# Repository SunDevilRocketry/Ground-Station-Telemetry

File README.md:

<h1>Ground Station Telemetry Unit</h1>

<p>Current PCB Revision: 1.0</p>
<p>PCB Part Number: A0005</p>

<p>The Ground Station Telemetry Unit adds wireless connectivity to the Raspberry-Pi 
based ground station computer. The unit is equipped with a socket for an XBee module, as well as a LoRa module.</p>

<p><b>Working Directory Structure:</b></p>

<p>
   doc: documentation
   
   src: source design files, e.g. schematic and PCB layout files

   lib: libraries for schematic symbols and footprints

   production: files needed for pcb fabrication, e.g. gerbers, profile, drill file

   sim: simulation models/files 

   cad: 3d models
  
   img: images of circuit/footprints for github display 
</p>

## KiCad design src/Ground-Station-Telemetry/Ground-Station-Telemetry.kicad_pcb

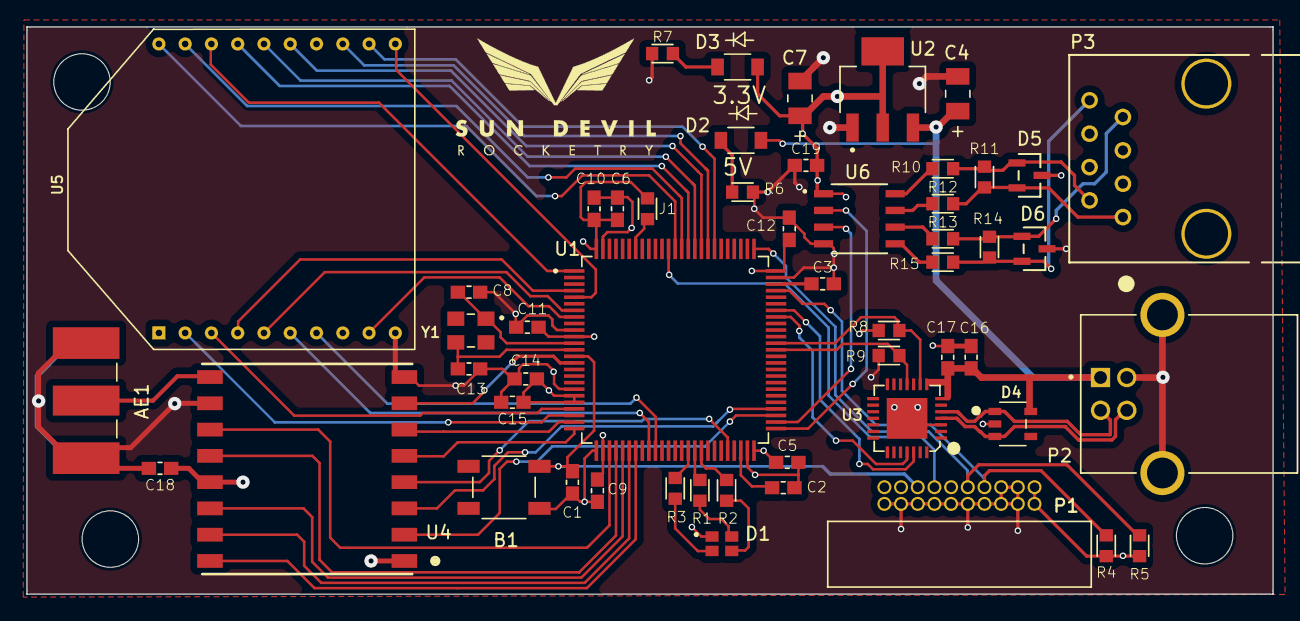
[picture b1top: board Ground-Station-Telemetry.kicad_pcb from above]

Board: 4 copper layers, 94.9 x 43.2 mm, 57 parts (0 on the bottom side), 64 nets.

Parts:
AE1: 142-0701-851
B1: PTS647SM38SMTR2LFS
C1, C5, C9, C10, C11, C12, C14, C17, C18, C19: 0.1uF; CAP_0603
C2, C3: 2.2uF; CAP_0603
C4, C7: 10uF; T491A106K010AT
C6: 4.7uF; CAP_0603
C8, C13: 8pF; CAP_0603
C15, C16: 1uF; CAP_0603
D1: CLMVC-FKA-CL1D1L71BB7C3C3
D2, D3: SML-LX1206GC-TR
D4: SP0504BAHTG
D5, D6: SMBJ36CA-13-F; CDSOT23-SM712
H1, H2, H4: Mounting-Hole; MountingHole_4.3mm_M4_DIN965
J1: Jumper_NO; RES_0603
LOGO1: Logo
P1: 3220-20-0200-00
P2: USB; USB-TypeB
P3: 54602-908LF
R1: 68; RES_0603
R2: 82; RES_0603
R3: 280; RES_0603
R4, R5: 100k; RES_0603
R6, R7: 240; RES_0603
R8: 4.7k; RES_0603
R9: 10k; RES_0603
R10, R12, R13, R15: 10; RES_0603
R11, R14: 100; RES_0603
U1: STM32H750VBTx; STM32H750VBT6
U2: LMS8117AMP-3.3_NOPB; LMS8117AMP-3.3NOPB
U3: CP2102-GMR(QFN28); CP2012-GMR
U4: RFM95W-868S2; RFM95
U5: XB24CDMPIT-001; XBee
U6: SN65HVD71DR
Y1: ECS-240-18-33-JGN-TR

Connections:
3.3V: C5.1, C6.1, C7.1, C9.1, C10.1, C11.1, C12.1, C14.1, C15.1, C18.1, C19.1, D1.1, D3.2, J1.1 (A), P1.1, P1.2, R4.2, R5.2, R8.1, U1.11 (VDD), U1.20 (VREF+), U1.21 (VDDA), U1.27 (VDD), U1.50 (VDD), U1.75 (VDD), U1.100 (VDD), U2.2 (VOUT), U4.13 (3_3V), U5.1 (VCC), U6.1 (VCC)
5V: C4.1, C16.1, C17.1, D2.2, D4.5, P2.1 (VCC), U2.3 (VIN), U3.7 (REGIN), U3.8 (VBUS)
/Connectivity/D+: D4.3, P2.3 (D+), U3.4 (D+)
/Connectivity/D-: D4.1, P2.2 (D-), U3.5 (D-)
A: D5.1, P3.2, R10.2, R11.2
B: D5.2, P3.1, R11.1, R12.2
BOOT: J1.2 (B), U1.94 (BOOT0)
CAP1: C2.1, U1.48 (VCAP1)
CAP2: C3.1, U1.73 (VCAP2)
Earth: AE1.2 (Shield), B1.1, C1.2, C2.2, C3.2, C4.2, C5.2, C6.2, C7.2, C8.2, C9.2, C10.2, C11.2, C12.2, C13.2, C14.2, C15.2, C16.2, C17.2, C18.2, C19.2, D4.2, D5.3, D6.3, P1.3, P1.4, P1.5, P1.6, P1.8, P1.10, P1.12, P1.14, P1.16, P1.18, P1.20, P2.4 (GND), P2.S1 (SHIELD), P2.S2 (SHIELD), R6.1, R7.1, R9.1, U1.10 (VSS), U1.19 (VSSA), U1.26 (VSS), U1.49 (VSS), U1.74 (VSS), U1.99 (VSS), U2.1 (GND), U3.3 (GND), U3.29 (PAD), U4.1 (GND), U4.8 (GND@1), U4.10 (GND@2), U5.10 (GND), U6.4 (GND)
LORA_IO0: U1.30 (PA6), U4.14 (DIO0)
LORA_IO1: U1.31 (PA7), U4.15 (DIO1)
LORA_IO2: U1.32 (PC4), U4.16 (DIO2)
LORA_IO3: U1.28 (PA4), U4.11 (DIO3)
LORA_IO4: U1.29 (PA5), U4.12 (DIO4)
LORA_IO5: U1.15 (PC0), U4.7 (DIO5)
LORA_MISO: U1.53 (PB14), U4.2 (MISO)
LORA_MOSI: U1.54 (PB15), U4.3 (MOSI)
LORA_RST: U1.24 (PA2), U4.6 (RESET)
LORA_SCK: U1.46 (PB10), U4.4 (SCK)
LORA_SS: U1.25 (PA3), U4.5 (NSS)
NRST: B1.3, C1.1, P1.15, U1.14 (NRST)
unnamed: AE1.1 (A), U4.9 (ANT)
unnamed: D1.2, R1.2
unnamed: D1.3, R2.2
unnamed: D1.4, R3.2
unnamed: D2.1, R6.2
unnamed: D3.1, R7.2
unnamed: R10.1, U6.8 (A)
unnamed: R12.1, U6.7 (B)
unnamed: R15.1, U6.5 (Y)
unnamed: R13.1, U6.6 (Z)
OSC_IN: C8.1, U1.12 (PH0), Y1.1
OSC_OUT: C13.1, U1.13 (PH1), Y1.3
RS485_RX: U1.51 (PB12), U6.2 (R)
RS485_TX: U1.52 (PB13), U6.3 (D)
STATUS_B: R1.1, U1.41 (PE11)
STATUS_G: R2.1, U1.42 (PE12)
STATUS_R: R3.1, U1.40 (PE10)
SWCLK: P1.9, R5.1, U1.76 (PA14)
SWDIO: P1.7, R4.1, U1.72 (PA13)
SWO: P1.13, U1.89 (PB3)
USB_RX: U1.68 (PA9), U3.25 (RXD)
USB_TX: U1.69 (PA10), U3.26 (TXD)
XBEE_DIO0: U1.88 (PD7), U5.20 (DIO0)
XBEE_DIO1: U1.87 (PD6), U5.19 (DIO1)
XBEE_DIO5: U1.84 (PD3), U5.15 (DI05)
XBEE_DIO6: U1.85 (PD4), U5.16 (DIO6)
XBEE_DIO7: U1.82 (PD1), U5.12 (DI07)
XBEE_DIO8: U1.8 (PC14), U5.9 (DI8)
XBEE_MISO: U1.4 (PE5), U5.4 (MISO)
XBEE_MOSI: U1.5 (PE6), U5.11 (MOSI)
XBEE_PWM0: U1.34 (PB0), U5.6 (PWM0)
XBEE_PWM1: U1.35 (PB1), U5.7 (PWM1)
XBEE_RX: U1.22 (PA0), U5.3 (RX)
XBEE_SCK: U1.1 (PE2), U5.18 (SCK)
XBEE_SS: U1.86 (PD5), U5.17 (SPI_SS)
XBEE_TX: U1.23 (PA1), U5.2 (TX)
Y: D6.2, P3.8, R14.1, R15.2
Z: D6.1, P3.7, R13.2, R14.2
~USB_RST: R8.2, U1.64 (PC7), U3.9 (~RST)
~USB_SUSPEND: R9.2, U1.63 (PC6), U3.11 (~SUSPEND)
~XBEE_RST: U1.7 (PC13), U5.5 (~RESET)
~XBEE_SLEEP: U1.83 (PD2), U5.13 (~SLEEP)

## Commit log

2022-10-11 created directory structure
2022-10-11 added information to readme
2022-10-11 added component symbols to library
2022-10-11 populated footprint library
2022-10-11 created rev1 schematic
2022-10-11 routed rev1
2023-04-09 added rs485 components to rev 2 lib files
2023-04-09 added RS485 transceiver to schematic
2023-04-09 finished initial rev 2 routing
2023-04-09 resolved DRC errors
2023-04-09 generated production files
2023-06-10 added PCB images to README

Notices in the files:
parts and their libraries:
Copyright 2021 Accelerated Designs. All rights reserved.
